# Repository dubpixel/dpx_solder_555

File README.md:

<!-- Improved compatibility of back to top link: See: https://github.com/othneildrew/Best-README-Template/pull/73 -->

<!--
*** Thanks for checking out the Best-README-Template. If you have a suggestion
*** that would make this better, please fork the repo and create a pull request
*** or simply open an issue with the tag "enhancement".
*** Don't forget to give the project a star!
*** Thanks again! Now go create something AMAZING! :D
-->

<!-- PROJECT SHIELDS -->
<!--
*** I'm using markdown "reference style" links for readability.
*** Reference links are enclosed in brackets [ ] instead of parentheses ( ).
*** See the bottom of this document for the declaration of the reference variables
*** for contributors-url, forks-url, etc. This is an optional, concise syntax you may use.
*** https://www.markdownguide.org/basic-syntax/#reference-style-links
-->
[![Contributors][contributors-shield]][contributors-url]
[![Forks][forks-shield]][forks-url]
[![Stargazers][stars-shield]][stars-url]
[![Issues][issues-shield]][issues-url]
[![MIT License][license-shield]][license-url]
[![LinkedIn][linkedin-shield]][linkedin-url]

<!-- PROJECT LOGO -->
<br />
<div align="center">

<h3 align="center">555 Solder or Die </h3>
<h3 align="center">2024 Hackfun Solder Challengee </h3>

  <p align="center">
    ...learn to solder down to 0402 or DIE trying!
    <br />
    <br />
    <br />
    <br />
    <a href="https://github.com/dubpixel/dpx_solder_555/tree/main/"><strong>Project Here!</strong></a>
     » 
    <a href="https://github.com/dubpixel/dpx_solder_555/tree/main/src/bom"><strong>BOM Here! »</strong></a>
     » 
    <a href="https://dubpixel.github.io/dpx_solder_555/ebom/index.html"><strong>Interactive BOM Here!</strong></a>
    <br />
    <br />
    <a href="https://github.com/dubpixel/dpx_solder_555/issues/new?labels=bug&template=bug-report---.md">Report Bug</a>
    ·
    <a href="https://github.com/dubpixel/dpx_solder_555/issues/new?labels=enhancement&template=feature-request---.md">Request Feature</a>
  </p>
</div>

<!-- TABLE OF CONTENTS -->
<details>
  <summary markdown="span">Table of Contents</summary>
  <ol>
    <li>
      <a href="#about-the-project">About The Project</a>
      <ul>
        <li><a href="#built-with">Built With</a></li>
      </ul>
    </li>
    <li>
      <a href="#getting-started">Getting Started</a>
      <ul>
        <li><a href="#prerequisites">Prerequisites</a></li>
        <li><a href="#installation">Installation</a></li>
      </ul>
    </li>
    <li><a href="#usage">Usage</a></li>
    <li><a href="#roadmap">Roadmap</a></li>
    <li><a href="#contributing">Contributing</a></li>
    <li><a href="#license">License</a></li>
    <li><a href="#contact">Contact</a></li>
    <li><a href="#acknowledgments">Acknowledgments</a></li>
  </ol>
</details>

<!-- ABOUT THE PROJECT -->
## About The Project

This is a learn to solder badge made for Hack Fun by @dubpixel - 
<br />
Hackfun is the Bushwick-based art-nerd meetup hosted every Wednesday. 
www.hackfun.com  - siliconcarnival@gmail.com

FRONT
![FRONT][product-front]

REAR
![REAR][product-rear]

iBOM PCB Front
![iBOM Front][product-pcbFront]

<p align="right">(<a href="#readme-top">back to top</a>)</p>

### Built With
* [![KiCad][KiCad.org]][KiCad-url]

<!--
 * [![Next][Next.js]][Next-url]
 * [![React][React.js]][React-url]
 * [![Vue][Vue.js]][Vue-url]
 * [![Angular][Angular.io]][Angular-url]
 * [![Svelte][Svelte.dev]][Svelte-url]
 * [![Laravel][Laravel.com]][Laravel-url]
 * [![Bootstrap][Bootstrap.com]][Bootstrap-url]
 * [![JQuery][JQuery.com]][JQuery-url]
-->
<p align="right">(<a href="#readme-top">back to top</a>)</p>

<!-- GETTING STARTED -->
## Getting Started

### Prerequisites

### Installation

1. Download...
2. Enjoy.
3. Repeat as Needed!
<!-- USAGE EXAMPLES -->
## Usage

<p align="right">(<a href="#readme-top">back to top</a>)</p>

<!-- ROADMAP -->
## Roadmap

- [ ] Feature 1
- [ ] Feature 2
- [ ] Feature 3
    - [ ] Nested Feature

See the [open issues](https://github.com/dubpixel/dpx_solder_555/issues) for a full list of proposed features (and known issues).

<p align="right">(<a href="#readme-top">back to top</a>)</p>

<!-- CONTRIBUTING -->
## Contributing

Contributions are what make the open source community such an amazing place to learn, inspire, and create. Any contributions you make are **greatly appreciated**.

If you have a suggestion that would make this better, please fork the repo and create a pull request. You can also simply open an issue with the tag "enhancement".
Don't forget to give the project a star! Thanks again!

1. Fork the Project
2. Create your Feature Branch (`git checkout -b feature/AmazingFeature`)
3. Commit your Changes (`git commit -m 'Add some AmazingFeature'`)
4. Push to the Branch (`git push origin feature/AmazingFeature`)
5. Open a Pull Request

<p align="right">(<a href="#readme-top">back to top</a>)</p>

### Top contributors:

<!-- LICENSE -->
## License

Distributed under the MIT License. See `LICENSE.txt` for more information.

<p align="right">(<a href="#readme-top">back to top</a>)</p>

<!-- CONTACT -->
## Contact

#Joshua Fleitell - i@dubpixel.tv

Project Link: [https://github.com/dubpixel/dpx_solder_555](https://github.com/dubpixel/dpx_solder_555)

<p align="right">(<a href="#readme-top">back to top</a>)</p>

<!-- ACKNOWLEDGMENTS -->
## Acknowledgments

* 
* 
* 

<p align="right">(<a href="#readme-top">back to top</a>)</p>

<!-- MARKDOWN LINKS & IMAGES -->
<!-- https://www.markdownguide.org/basic-syntax/#reference-style-links -->
[contributors-shield]: https://img.shields.io/github/contributors/dubpixel/dpx_solder_555.svg?style=for-the-badge
[contributors-url]: https://github.com/dubpixel/dpx_solder_555/graphs/contributors
[forks-shield]: https://img.shields.io/github/forks/gdubpixel/dpx_solder_555.svg?style=for-the-badge
[forks-url]: https://github.com/dubpixel/dpx_solder_555/network/members
[stars-shield]: https://img.shields.io/github/stars/dubpixel/dpx_solder_555.svg?style=for-the-badge
[stars-url]: https://github.com/dubpixel/dpx_solder_555/stargazers
[issues-shield]: https://img.shields.io/github/issues/dubpixel/dpx_solder_555.svg?style=for-the-badge
[issues-url]: https://github.com/dubpixel/dpx_solder_555/issues
[license-shield]: https://img.shields.io/github/license/dubpixel/dpx_solder_555.svg?style=for-the-badge
[license-url]: https://github.com/dubpixel/dpx_solder_555/blob/master/LICENSE.txt
[linkedin-shield]: https://img.shields.io/badge/-LinkedIn-black.svg?style=for-the-badge&logo=linkedin&colorB=555
[linkedin-url]: https://linkedin.com/in/linkedin_username
[product-screenshot]: images/screenshot.png
[product-front]: images/front.png
[product-rear]: images/rear.png
[product-pcbFront]: images/pcb_front.png
[Next.js]: https://img.shields.io/badge/next.js-000000?style=for-the-badge&logo=nextdotjs&logoColor=white
[Next-url]: https://nextjs.org/
[React.js]: https://img.shields.io/badge/React-20232A?style=for-the-badge&logo=react&logoColor=61DAFB
[React-url]: https://reactjs.org/
[Vue.js]: https://img.shields.io/badge/Vue.js-35495E?style=for-the-badge&logo=vuedotjs&logoColor=4FC08D
[Vue-url]: https://vuejs.org/
[Angular.io]: https://img.shields.io/badge/Angular-DD0031?style=for-the-badge&logo=angular&logoColor=white
[Angular-url]: https://angular.io/
[Svelte.dev]: https://img.shields.io/badge/Svelte-4A4A55?style=for-the-badge&logo=svelte&logoColor=FF3E00
[Svelte-url]: https://svelte.dev/
[Laravel.com]: https://img.shields.io/badge/Laravel-FF2D20?style=for-the-badge&logo=laravel&logoColor=white
[Laravel-url]: https://laravel.com
[Bootstrap.com]: https://img.shields.io/badge/Bootstrap-563D7C?style=for-the-badge&logo=bootstrap&logoColor=white
[Bootstrap-url]: https://getbootstrap.com
[JQuery.com]: https://img.shields.io/badge/jQuery-0769AD?style=for-the-badge&logo=jquery&logoColor=white
[JQuery-url]: https://jquery.com 
[KiCad.org]: https://img.shields.io/badge/KiCad-v8.0.3-blue
[KiCad-url]: https://kicad.org

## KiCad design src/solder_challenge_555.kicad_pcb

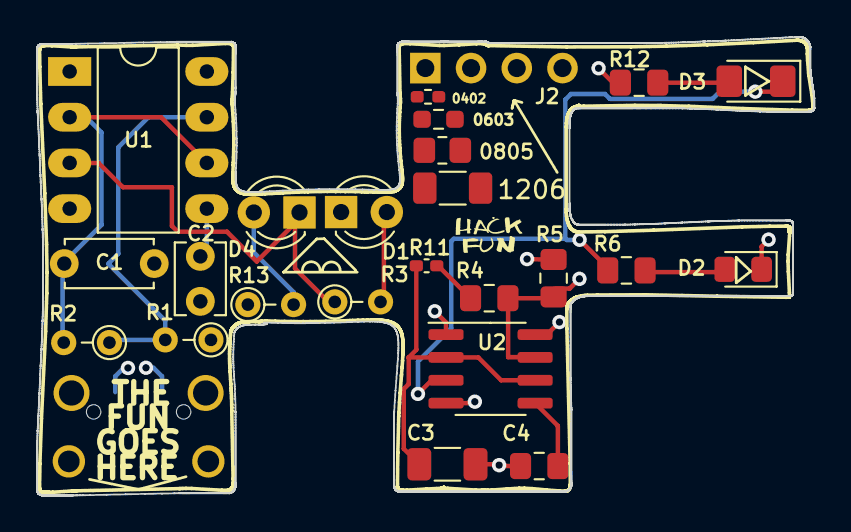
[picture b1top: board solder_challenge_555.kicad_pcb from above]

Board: 4 copper layers, 43.2 x 25.5 mm, 25 parts (1 on the bottom side), 15 nets.

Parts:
C1: 10uF; C_Disc_D4.7mm_W2.5mm_P5.00mm
C2: 10nf; C_Disc_D3.8mm_W2.6mm_P2.50mm
C3: 10uf; C_1206_3216Metric_Pad1.33x1.80mm_HandSolder
C4: .01uf; C_0805_2012Metric_Pad1.18x1.45mm_HandSolder
D1, D4: LED; LED_D3.0mm
D2: LED; LED_0805_2012Metric_Pad1.15x1.40mm_HandSolder
D3: LED; LED_1206_3216Metric_Pad1.42x1.75mm_HandSolder
J1: USB_B_Micro; USB_Micro-B_Wuerth_629105150521_CircularHoles
J2: Conn_01x04_Socket; PinSocket_1x04_P2.54mm_Vertical
R1: 1k; R_Axial_DIN0204_L3.6mm_D1.6mm_P2.54mm_Vertical
R2: 20k; R_Axial_DIN0204_L3.6mm_D1.6mm_P2.54mm_Vertical
R3, R13: 330; R_Axial_DIN0204_L3.6mm_D1.6mm_P2.54mm_Vertical
R4: 20k; C_0805_2012Metric_Pad1.18x1.45mm_HandSolder
R5: 1k; C_0805_2012Metric_Pad1.18x1.45mm_HandSolder
R6, R12: 330; C_0805_2012Metric_Pad1.18x1.45mm_HandSolder
R7: 1206; R_1206_3216Metric_Pad1.30x1.75mm_HandSolder
R8: 0805; R_0805_2012Metric_Pad1.20x1.40mm_HandSolder
R9: 0603; R_0603_1608Metric_Pad0.98x0.95mm_HandSolder
R10: 0402; R_0402_1005Metric_Pad0.72x0.64mm_HandSolder
R11: 20k; C_0402_1005Metric_Pad0.74x0.62mm_HandSolder
U1: DIP-8_W7.62mm_LongPads
U2: SOIC-8_3.9x4.9mm_P1.27mm

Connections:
/smt_555/2: C3.1, R11.2, U2.2 (TR), U2.6 (THR)
/smt_555/3: D3.1 (K), R6.1, U2.3 (Q)
/smt_555/5: C4.1, U2.5 (CV)
/smt_555/7: R4.1, R5.2, U2.7 (DIS)
GND: C1.2, C2.2, C3.2, C4.2, D1.1 (K), D2.1 (K), J1.5 (GND), J2.4, U1.1 (GND), U2.1 (GND)
unnamed: D1.2 (A), R3.2
unnamed: D2.2 (A), R6.2
unnamed: D3.2 (A), R12.2
unnamed: D4.2 (A), R13.2
unnamed: D4.1 (K), R3.1, U1.3 (Q)
unnamed: R4.2, R11.1
unnamed: C2.1, U1.5 (CV)
unnamed: R1.2, R2.1, U1.7 (DIS)
unnamed: C1.1, R2.2, U1.2 (TR), U1.6 (THR)
VCC: J1.1 (VBUS), J2.1, R1.1, R5.1, R12.1, R13.1, U1.4 (R), U1.8 (VCC), U2.4 (R), U2.8 (VCC)

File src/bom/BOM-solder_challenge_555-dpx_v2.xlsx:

Value | Designator | Footprint | Footprint Long | Y | LCSC |  | alternate | I |  | X
THRU HOLE PARTS
USB-A BOB | j2 | 1X4 HEADER BOB |  |  | AMAZON
1x04 Pin 2.54 | J2 | 1x4 Pin Head | PinSocket_1x04_P2.54mm_Vertical |  | house
555 dip-8 | U1 | DIP-8 IC | DIP-8_W7.62mm_LongPads |  | C398063
10uF | C1 | Ceramic P5 | C_Disc_D4.7mm_W2.5mm_P5.00mm |  | C454403
10nf | C2 | Ceramic p2.5 | C_Disc_D3.8mm_W2.6mm_P2.50mm |  | C2832505 |  | C353903
1k | R1 | 1/8w R TH | R_Axial_DIN0204_L3.6mm_D1.6mm_P2.54mm_Vertical |  | C5249394
330 | R13, R3 | 1/8w R TH | R_Axial_DIN0204_L3.6mm_D1.6mm_P2.54mm_Vertical |  | C2848567
20k | R2 | 1/8w R TH | R_Axial_DIN0204_L3.6mm_D1.6mm_P2.54mm_Vertical |  | C119208
LED | D1 | 3.0mm led | LED_D3.0mm |  | C5172928
LED | D4 | 3.0mm led | LED_D3.0mm |  | C3028824
SMT PARTS
20k | R4 | Resist 0805 | C_0805_2012Metric_Pad1.18x1.45mm_HandSolder |  | C4328
1k | R5 | Resist 0805 | C_0805_2012Metric_Pad1.18x1.45mm_HandSolder |  | amazon
330 | R6, R12 | Resist 0805 | C_0805_2012Metric_Pad1.18x1.45mm_HandSolder |  | C17630
20k | R11 | Resist 0402 | C_0402_1005Metric_Pad0.74x0.62mm_HandSolder |  | C25765
 | r11 CAN BE OMITTED/BRIDGED
330 | R12 | Resist 0805 | C_0805_2012Metric_Pad1.18x1.45mm_HandSolder |  | C17630
10uf | C3 | 1206 cap | C_1206_3216Metric_Pad1.33x1.80mm_HandSolder |  | C13585
10nf | C4 | 0805 cap | C_0805_2012Metric_Pad1.18x1.45mm_HandSolder |  | C83170
LED | D2 | 0805 led | LED_0805_2012Metric_Pad1.15x1.40mm_HandSolder |  | C20608785 |  | C2293
LED | D3 | 1206 led | LED_1206_3216Metric_Pad1.42x1.75mm_HandSolder |  | C49018 |  | C84270
555 soic | U2 | SOIC-8 | SOIC-8_3.9x4.9mm_P1.27mm |  | C7593
USB_B_Micro | REAR-LABEL | Micro-USB | USB_Micro-B_Wuerth_629105150521_CircularHoles |  | amazon
OPTIONAL PARTS (FOR fun)
10k | R7 | Resist 1206 | R_1206_3216Metric_Pad1.30x1.75mm_HandSolder |  | C17902 |  | x
10k | R8 | Resist 0805 | R_0805_2012Metric_Pad1.20x1.40mm_HandSolder |  | C17414 |  | x
10k | R9 | Resist 0603 | R_0603_1608Metric_Pad0.98x0.95mm_HandSolder |  | C25804 |  | x
20k | R10 | Resist 0402 | R_0402_1005Metric_Pad0.72x0.64mm_HandSolder |  | C25765 |  | x

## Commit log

2024-09-22 more readme updates
2024-09-22 trying to get bom as webpage
    This reverts commit e49a391bcf503e1371748bd8b984c281e54055b7.
2024-09-22 directory rename and readme edits
2024-09-22 i suck at html
2024-09-22 logo update
2024-09-22 ibom url updarte
2024-09-22 photo and stuff
2024-09-23 added PCB image from iBom + readme
2024-09-23 reorganize, dircetory cleanup + readme
2024-09-23 update production files
2024-09-30 v 1 dot 5 for real
    i left the qr code off the back... woooo
2024-11-12 Create LICENSE
2024-11-12 Rename LICENSE to LICENSE.txt
2024-11-13 local bom changes and autosave
2024-11-13 uhhhh
2024-11-13 Update logo in readme
2024-12-05 change case sensitive dpx_solder_555
2024-12-05 more readme corrections
2024-12-07 Create Gemfile
2024-12-07 trying to make some space
2024-12-07 Update README.md
    trying to get the markdown decode to work differently
2024-12-07 Update Gemfile
